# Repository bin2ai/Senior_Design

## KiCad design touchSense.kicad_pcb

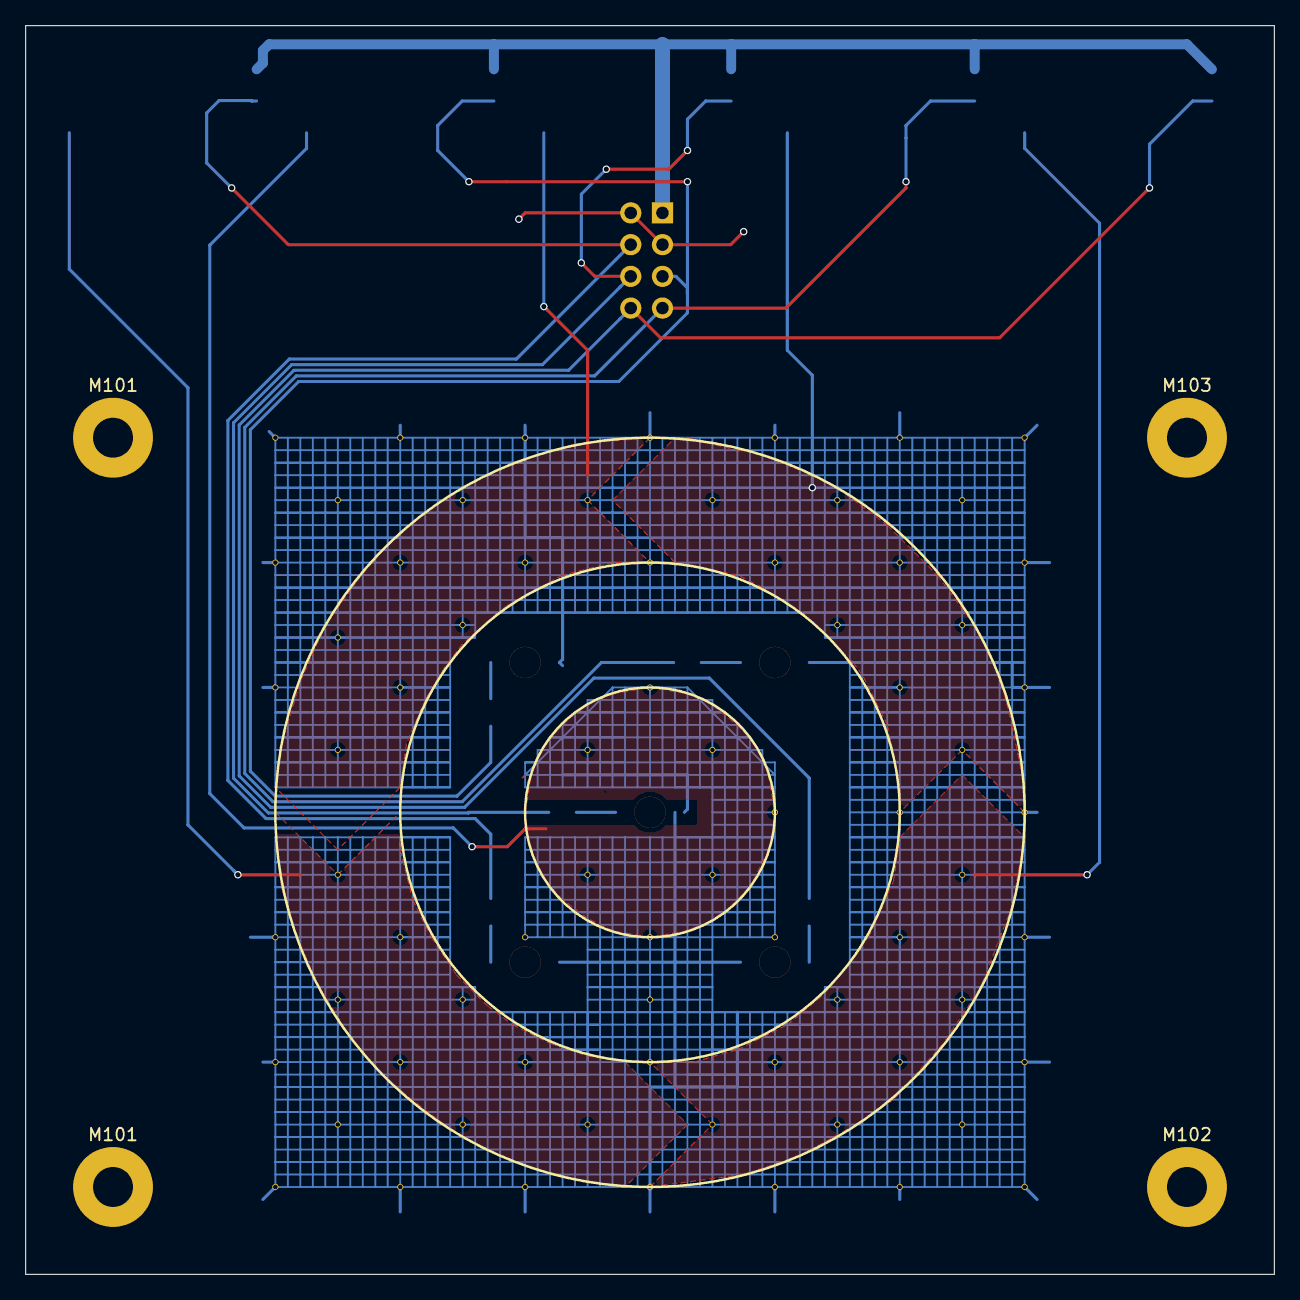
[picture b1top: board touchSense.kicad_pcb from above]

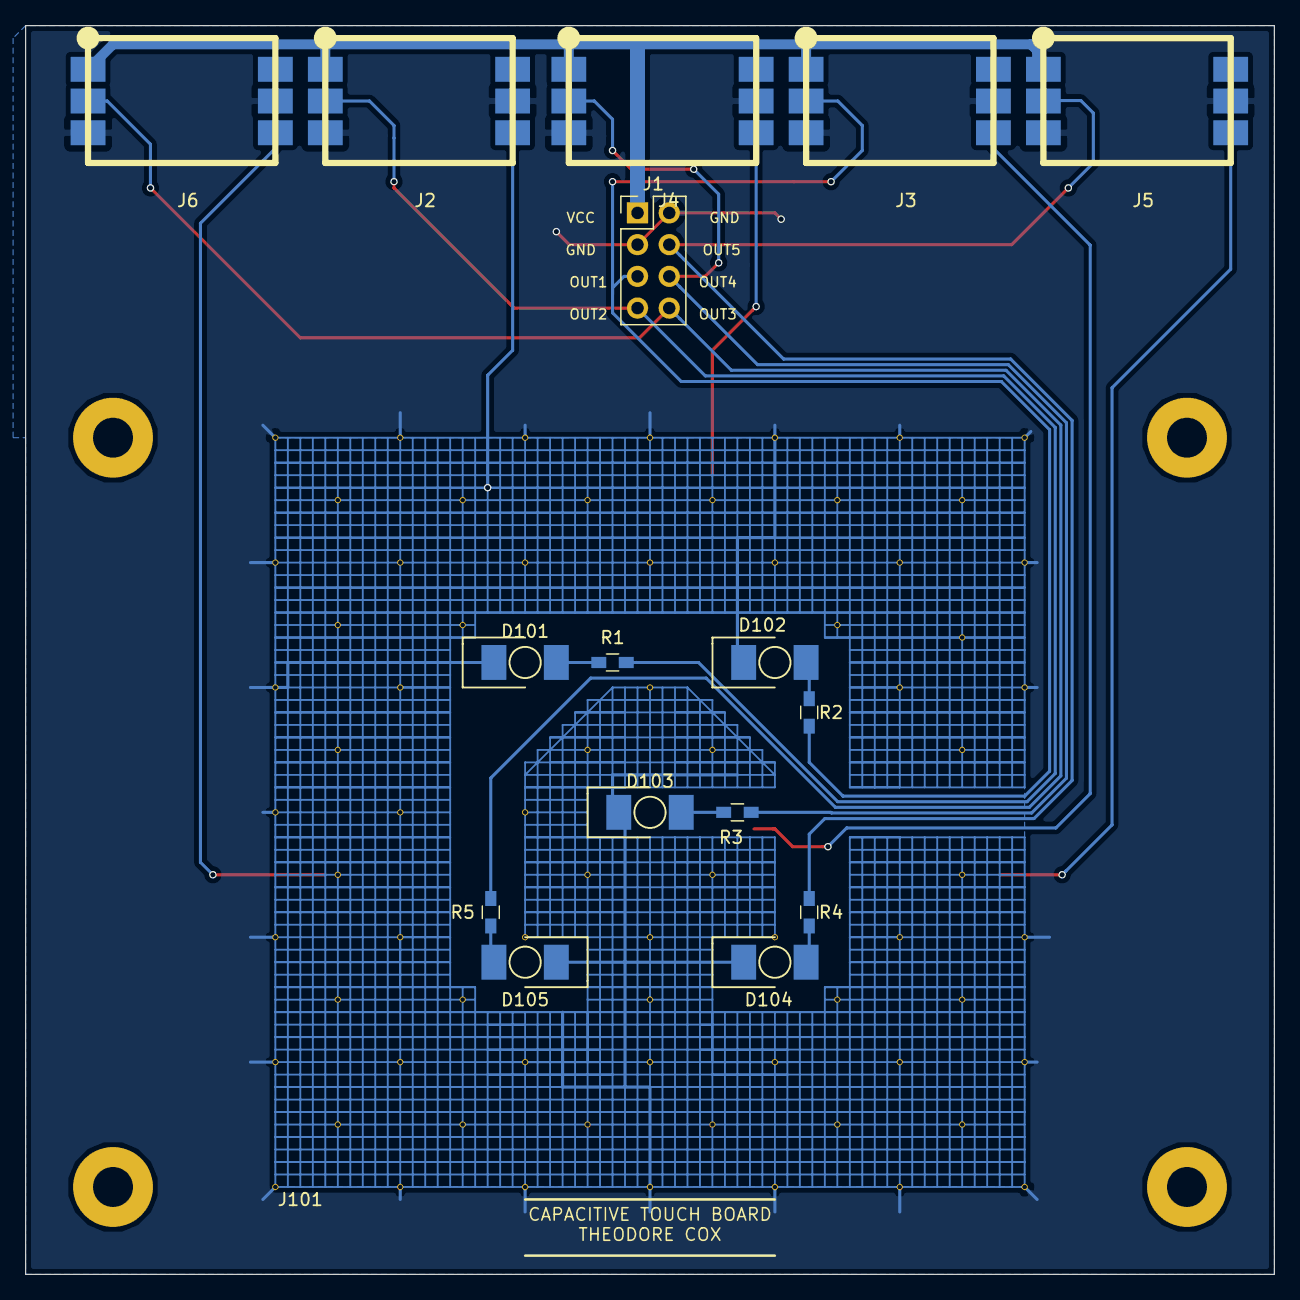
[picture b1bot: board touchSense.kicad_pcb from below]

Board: 2 copper layers, 100.0 x 100.0 mm, 21 parts (17 on the bottom side), 12 nets.

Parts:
D101, D102, D103, D104, D105: LED; LED_VLRK31Q1R2_REV_GUL
J1: breakout_MainBoard; Pin_Header_Straight_2x04_Pitch2.54mm
J2, J3, J4, J5, J6: CAPTOUC_castellated_Module; CAPTOUCH_castellated
J101: HATCHED_FILL; HATCHED_FILL_60mm_signalRouting
M101, M101#2, M102, M103: Mount; MountingHole_3.2mm_M3_Pad
R1, R2, R3, R4, R5: 500; R_0603_HandSoldering

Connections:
/OUT_1: J1.7, J2.2, R1.2
/OUT_2: J1.5, J3.2, R2.2
/OUT_3: J1.6, J4.2, R3.2
/OUT_4: J1.4, J5.2, R4.2
/OUT_5: J1.8, J6.2, R5.2
/VCC: J1.1, J2.1, J3.1, J4.1, J5.1, J6.1
GND: D101.1, D102.1, D103.1, D104.1, D105.1, J1.2, J1.3, J2.3, J2.5, J3.3, J3.5, J4.3, J4.5, J5.3, J5.5, J6.3, J6.5, J101.1
unnamed: D101.2, R1.1
unnamed: D102.2, R2.1
unnamed: D103.2, R3.1
unnamed: D104.2, R4.1
unnamed: D105.2, R5.1

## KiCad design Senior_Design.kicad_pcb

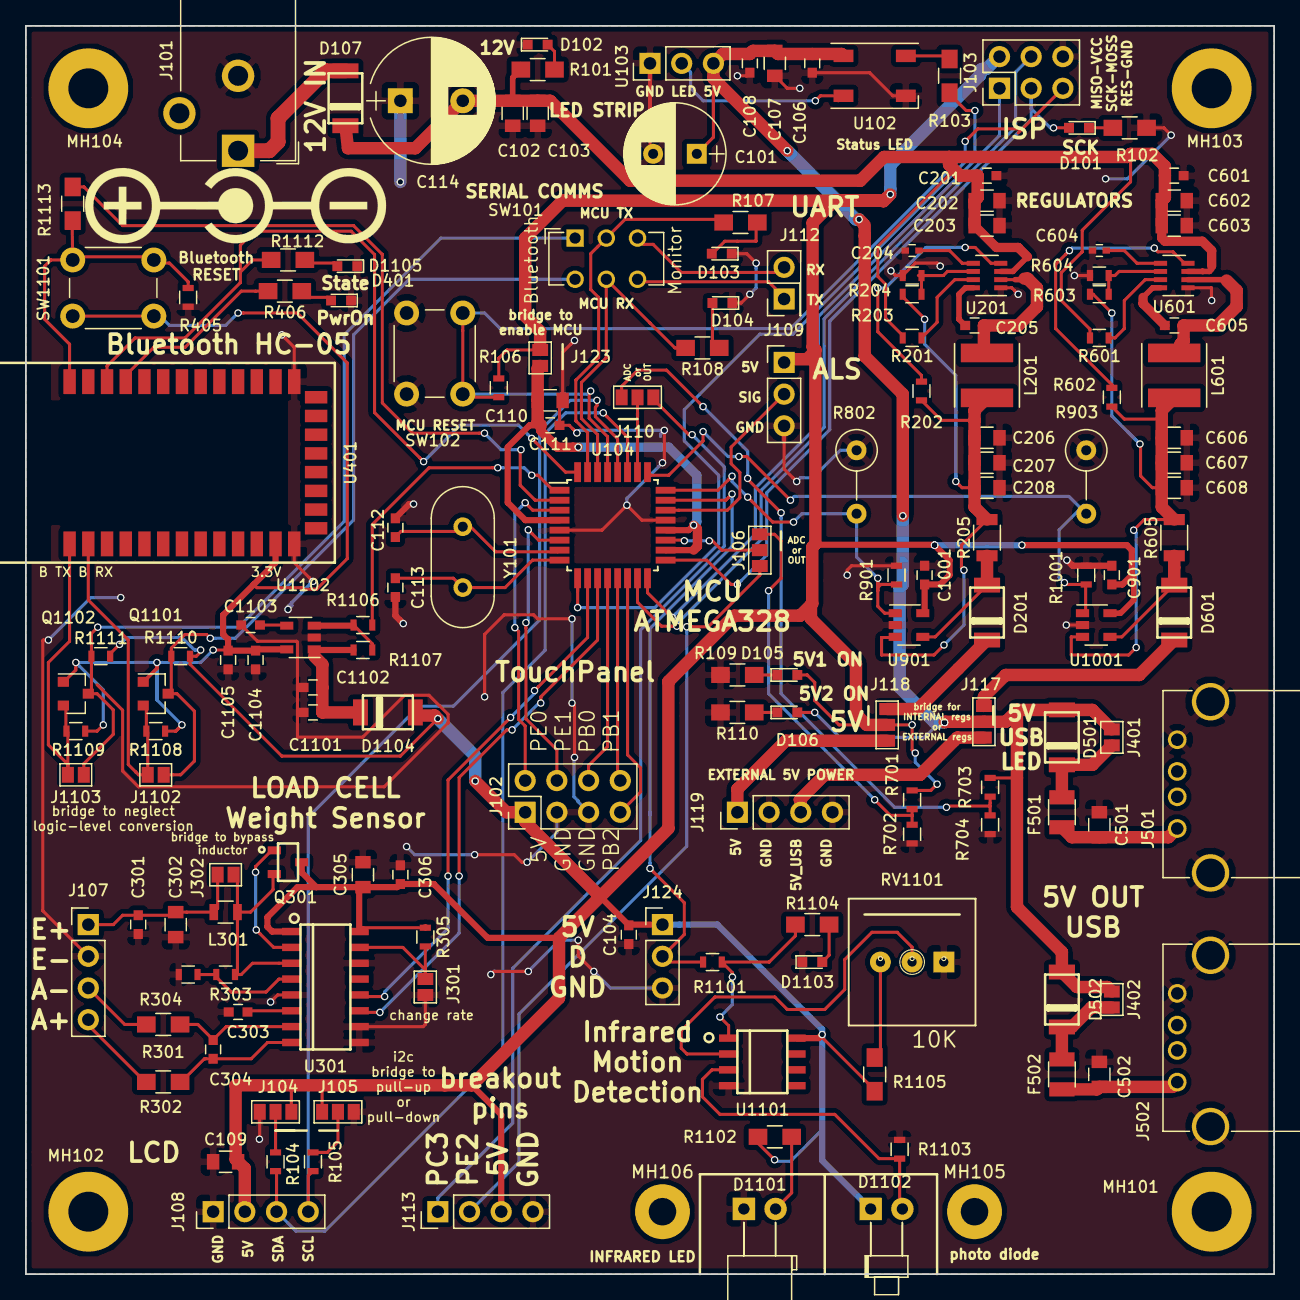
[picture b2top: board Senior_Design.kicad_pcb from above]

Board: 2 copper layers, 100.0 x 100.0 mm, 164 parts (0 on the bottom side), 101 nets.

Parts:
C101: ?uF; CP_Radial_D8.0mm_P3.50mm
C102, C103, C107, C109, C110, C202, C203, C302, C305, C501, C502, C602, C603: 10uF; C_0805
C104, C106, C108, C111, C201, C205, C301, C303, C304, C306, C601, C605, C901, C1001, C1101, C1103, C1104: 0.1uF; C_0603
C112, C113: 20pF; C_0603
C114: ?uF; CP_Radial_D10.0mm_P5.00mm
C204, C604: 8200pF; C_0402
C206, C207, C208, C606, C607, C608: 22uF; C_0805
C1102, C1105: 1uF; C_0603
D101, D102, D103, D104, D105, D106, D401, D1103, D1105: LED; LED_0603
D107, D201, D501, D502, D601, D1104: D_Schottky; SOD-128
D1101: IR204A; LED_D5.0mm_Horizontal_O3.81mm_Z3.0mm
D1102: D_Photo; LED_D1.8mm_W1.8mm_H2.4mm_Horizontal_O3.81mm_Z4.9mm
F501, F502: Polyfuse; Fuse_SMD1206_Reflow
J101: BARREL_JACK; Barrel_Jack_CUI_PJ-102AH
J102: touch(8pos) AT42QT1070 STANDALONE; Pin_Header_Straight_2x04_Pitch2.54mm
J103: ISP; Pin_Header_Straight_2x03_Pitch2.54mm
J104, J105, J106, J110, J117, J118: GS3
J107: LoadCell_Conn; Pin_Header_Straight_1x04_Pitch2.54mm
J108: Smraza2004_LCD; Pin_Header_Straight_1x04_Pitch2.54mm
J109: ambientLight; Pin_Header_Straight_1x03_Pitch2.54mm
J112: Serial Monitor; Pin_Header_Straight_2x01_Pitch2.54mm
J113: breakout; Pin_Header_Straight_1x04_Pitch2.54mm
J119: ext_5VPWR; Pin_Header_Straight_1x04_Pitch2.54mm
J123, J301, J302, J401, J402, J1102, J1103: GS2
J124: ext_Motion; Pin_Header_Straight_1x03_Pitch2.54mm
J501, J502: USB_A
L201, L601: 4.7uH; L_Taiyo-Yuden_MD-5050
L301: 3.3uH; L_0805
MH101, MH102, MH103, MH104: Mounting Hole; MountingHole_3.2mm_M3_Pad
MH105, MH106: IR LIGHT BLOCKER MOUNT; MountingHole_2.2mm_M2_Pad
Q301: MMBT4403; SOT23
Q1101, Q1102: BSS138; SOT-23
R101, R102, R103, R107, R108, R109, R110, R406, R1102, R1104, R1112, R1113: 500; R_0805_HandSoldering
R104, R105, R1107: 100K; R_0603
R106, R201, R601, R701, R702, R703, R704, R1101: 10k; R_0603
R202, R602: 100k; R_0603
R203, R603: 59k; R_0603
R204, R604: 10k_FB; R_0603
R205, R605: 0.1_SHUNT; R_1206
R301, R302, R1105: 100; R_0805_HandSoldering
R303: 20K; R_0603
R304: 8.2K; R_0603
R305, R405, R901, R1001, R1106, R1108, R1109, R1110, R1111: 10K; R_0603
R802, R903: RL; R_Axial_DIN0309_L9.0mm_D3.2mm_P5.08mm_Vertical
R1103: 54.9K; R_0603
RV1101: 10K; TSR-3386U
SW101: Serial Switch; SW_CuK_JS202011CQN_DPDT_Straight
SW102: RESET; SW_PUSH_6mm
SW1101: BLE_RESET; SW_PUSH_6mm
U102: WS2812B; LED_WS2812B-PLCC4
U103: WS2812B_STRIP; Pin_Header_Straight_1x03_Pitch2.54mm
U104: ATMEGA328PB-AU; TQFP-32_7x7mm_Pitch0.8mm
U201, U601: TPS563210ADDFT; SOT-23-8
U301: HX711; SOIC16
U401: MOUDLE-BLUETOOTH-HC-05(34P-27X13MM); HC-05
U901, U1001: INA169; SOT-23-5
U1101: LM358_IC; SOIC8
U1102: LP2985-3.3; SOT-23-5
Y101: 16MHZ; Crystal_HC49-U_Vertical

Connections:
5V1_monADC: J106.1, R701.2, R702.1
5V2_monADC: J110.1, R703.2, R704.1
5V-BUS: C104.2, C109.1, C305.2, C306.1, C901.1, C1001.1, D105.2, D1102.1, D1104.2, J102.1, J103.2, J104.3, J105.3, J108.2, J109.1, J113.3, J118.2, J123.2, J124.1, Q301.3, R106.1, R305.1, R701.1, R1102.1, R1105.1, R1110.2, R1111.2, U301.1, U301.16, U901.5, U1001.5, U1101.8
5V-BUS_USBLINE: C101.1, C106.2, C107.2, C108.2, D106.2, D501.2, D502.2, J117.2, J401.1, J402.1, R703.1, U102.1, U103.3
5V_curMon+: C206.1, C207.1, C208.1, L201.2, R202.1, R203.2, R205.2, U901.3
5V_curMon+_USBLINE: C606.1, C607.1, C608.1, L601.2, R602.1, R603.2, R605.2, U1001.3
5V_curMon-: D201.2, R205.1, U901.4
5V_curMon-_USBLINE: D601.2, R605.1, U1001.4
5V_curMon_ADC: R802.2, R901.2, U104.24, U901.1
5V_curMon_USBLINE_ADC: R903.2, R1001.2, U104.25, U1001.1
+12V: C102.1, C103.1, C114.2, C201.1, C202.1, C203.1, C601.1, C602.1, C603.1, D107.1, R101.2, R201.2, R601.2, U201.3, U601.3
/Bluetooth/3_3V: C1104.2, C1105.2, Q1101.1, Q1102.1, R1108.2, R1109.2, SW1101.2, U401.12, U1102.5
/Bluetooth/PwrOn: R406.2, U401.31
/Bluetooth/RX_3v3: J1102.2, Q1101.2, R1108.1, U401.2
/Bluetooth/TX_3v3: J1103.2, Q1102.2, R1109.1, U401.1
/RX: J112.2, SW101.3
/TX: J112.1, SW101.6
/_5V_SYS: D201.1, J118.1
/_5V_USB: D601.1, J117.1
BT_EN: R1106.2, U104.1
BT_KEY: R1113.2, U104.2
BT_STATE: R1112.2, U104.32, U401.32
B_RX: J1103.1, Q1102.3, R1111.1, SW101.1
B_TX: J1102.1, Q1101.3, R1110.1, SW101.4
GND: C101.2, C102.2, C103.2, C104.1, C106.1, C107.1, C108.1, C109.2, C110.1, C111.1, C112.2, C113.2, C114.1, C201.2, C202.2, C203.2, C204.2, C206.2, C207.2, C208.2, C301.2, C302.2, C303.2, C305.1, C306.2, C501.2, C502.2, C601.2, C602.2, C603.2, C604.2, C606.2, C607.2, C608.2, C901.2, C1001.2, C1101.1, C1102.1, C1103.1, C1104.1, C1105.1, D102.1, D103.1, D104.1, D401.1, D1101.1, D1103.1, D1105.1, J101.2, J102.3, J102.5, J103.6, J104.1, J105.1, J107.2, J108.1, J109.3, J113.4, J119.2, J119.4, J124.3, J301.2, J501.4, J501.5, J502.4, J502.5, R102.2, R109.2, R110.2, R204.1, R304.2, R405.1, R604.1, R702.2, R704.2, R802.1, R901.1, R903.1, R1001.1, R1103.2, RV1101.1, SW102.2, U102.3, U103.1, U104.5, U104.21, U201.1, U301.5, U301.9, U301.10, U301.14, U401.13, U401.22, U601.1, U901.2, U1001.2, U1101.4, U1102.2
LEDS_Din: U102.2, U103.2
LED_Din: R103.1, U104.9
MCU_RX: R108.2, SW101.5, U104.30
MCU_TX: R107.2, SW101.2, U104.31
MISO: J103.1, U104.16
MOSI: J103.4, U104.15
Motion_Signal: J124.2, R1101.2, U104.23
unnamed: C110.2, C111.2, J123.1, U104.4, U104.18, U104.20
unnamed: C112.1, U104.7, Y101.2
unnamed: C113.1, U104.8, Y101.1
unnamed: C204.1, U201.5
unnamed: C205.1, U201.8
unnamed: C205.2, L201.1, U201.2
unnamed: C303.1, U301.6
unnamed: C304.1, R301.1, U301.7
unnamed: C304.2, R302.1, U301.8
unnamed: C501.1, F501.2, J501.1
unnamed: C502.1, F502.2, J502.1
unnamed: C604.1, U601.5
unnamed: C605.1, U601.8
unnamed: C605.2, L601.1, U601.2
unnamed: C1101.2, C1102.2, D1104.1, R1107.1, U1102.1
unnamed: C1103.2, U1102.4
unnamed: D101.1, R102.1
unnamed: D102.2, R101.1
unnamed: D103.2, R107.1
unnamed: D104.2, R108.1
unnamed: D105.1, R109.1
unnamed: D106.1, R110.1
unnamed: D107.2, J101.1
unnamed: D401.2, R406.1
unnamed: D501.1, F501.1, J401.2
unnamed: D502.1, F502.1, J402.2
unnamed: D1101.2, R1102.2
unnamed: D1102.2, R1103.1, U1101.3
unnamed: D1103.2, R1104.2
unnamed: D1105.2, R1112.1
unnamed: J104.2, R104.2
unnamed: J105.2, R105.2
unnamed: J106.2, U104.19
unnamed: J110.2, U104.26
unnamed: J117.3, J119.3
unnamed: J118.3, J119.1
unnamed: J301.1, R305.2, U301.15
unnamed: J302.1, L301.2, Q301.2, R303.1, U301.3
unnamed: Q301.1, U301.2
unnamed: R103.2, U102.4
unnamed: R201.1, U201.7
unnamed: R202.2, U201.4
unnamed: R203.1, R204.2, U201.6
unnamed: R303.2, R304.1, U301.4
unnamed: R601.1, U601.7
unnamed: R602.2, U601.4
unnamed: R603.1, R604.2, U601.6
unnamed: R1101.1, R1104.1, U1101.1
unnamed: R1105.2, RV1101.3
unnamed: R1106.1, R1107.2, U1102.3
unnamed: R405.2, R1113.1, SW1101.1, U401.34
unnamed: RV1101.2, U1101.2
RESET: J103.5, R106.2, SW102.1, U104.29
SCALE_A+: J107.4, R302.2
SCALE_A-: J107.3, R301.2
SCALE_DOUT: U104.10, U301.12
SCALE_E+: C301.1, C302.1, J107.1, J302.2, L301.1
SCALE_PD_SCK: U104.11, U301.11
SCK: D101.2, J103.3, U104.17
SCL: J108.4, R105.1, U104.28
SDA: J108.3, R104.1, U104.27
ambientLight: J109.2, U104.22
breakout_1A: J110.3, J113.1
breakout_2A: J106.3, J113.2
touch_1: J102.6, U104.12
touch_2: J102.8, U104.13
touch_3: J102.7, U104.14
touch_4: J102.2, U104.3
touch_5: J102.4, U104.6

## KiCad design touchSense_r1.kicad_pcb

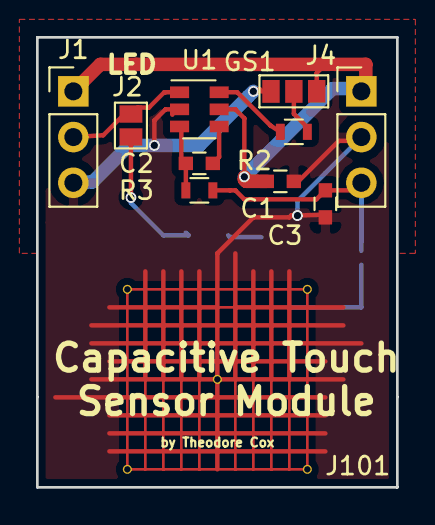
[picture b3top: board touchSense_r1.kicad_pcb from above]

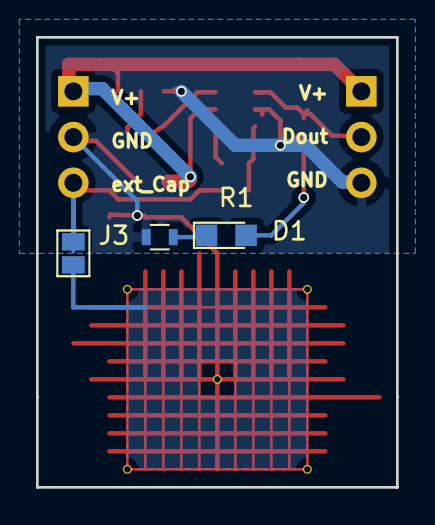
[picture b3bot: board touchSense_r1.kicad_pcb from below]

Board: 2 copper layers, 20.0 x 25.0 mm, 14 parts (3 on the bottom side), 10 nets.

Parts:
C1: 0.1uF; C_0603
C2: 4.7nF; C_0603
C3: 5pF; C_0603
D1: LED; LED_0805
GS1: GS3
J1: breakout; Pin_Header_Straight_1x03_Pitch2.54mm
J2, J3: GS2
J4: cap/daisy; Pin_Header_Straight_1x03_Pitch2.54mm
J101: Hatched_Fill; HATCHED_FILL_10mm
R1, R2: 1K; R_0603
R3: 10K; R_0603
U1: AT42QT1010-TSHR; SOT-23-6

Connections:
/CAP_PAD: C3.1, J3.1, J4.3, R3.1
/OUT1: J1.2, J2.2, U1.1
/VDD: C1.1, GS1.1, J1.1, J4.1, U1.5
GND: C1.2, C3.2, GS1.3, J1.3, J4.2, J101.1, R1.1, U1.2
unnamed: C2.1, R3.2, U1.3
unnamed: C2.2, U1.4
unnamed: D1.1, R1.2
unnamed: D1.2, J2.1
unnamed: GS1.2, R2.1
unnamed: R2.2, U1.6

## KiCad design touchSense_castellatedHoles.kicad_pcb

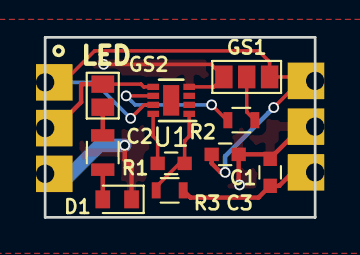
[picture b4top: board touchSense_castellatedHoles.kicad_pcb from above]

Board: 2 copper layers, 15.0 x 10.0 mm, 12 parts (0 on the bottom side), 9 nets.

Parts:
C1: 0.1uF; C_0603
C2: 4.7nF; C_0603
C3: 5pF; C_0603
D1: LED_0603_1608Metric
GS1: GS3
GS2: GS2
J1: breakout; CONN_01x03_CastellatedHole_Pad_1mmDrill
J?: CONN_01X03_CASTELLATED; CONN_01x03_CastellatedHole_Pad_1mmDrill
R1: R_0805
R2: 1K; R_0603
R3: 10K; R_0603
U1: VDFN-8-1EP_2x2mm_Pitch0.5mm

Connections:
/CAP_PAD: C3.1, J?.6, R3.1
/OUT1: GS2.2, J1.2, U1.5
/VDD: C1.1, GS1.1, J1.1, J?.4, U1.7
GND: C1.2, C3.2, D1.1, GS1.3, J1.3, J?.5, U1.4
unnamed: C2.1, R3.2, U1.1
unnamed: C2.2, U1.8
unnamed: GS2.1, R1.1
unnamed: GS1.2, R2.1
unnamed: R2.2, U1.6

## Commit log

2018-04-23 aded motion sense sheet
2018-04-23 new touch sense schematic
    different part AT42QT1010/1011
2018-04-23 changed to ATMEGA2560
2018-04-23 added usb-serial schematic
2018-04-24 added 12V power schematic
2018-04-24 created current monitor schematic
2018-04-24 current Monitor schematic edit
2018-04-24 last edit of the night 4-24
2018-04-24 added bom current as of 4-24
2018-04-24 bom format fix
2018-04-24 added FTDI chip to bom
2018-05-13 started PCB layout
2018-05-14 hc-05 and buzzer 3d model
2018-06-01 after group meeting
2018-06-05 MCU Change ATMEGA328PB
2018-06-05 all components on board, needs routing
2018-06-06 before meeting
2018-06-07 traces started
2018-06-08 99 percent ready to order
2018-06-09 finalized pcblayouts, before uploading to manufacturer
2018-06-10 new touch implementation
2018-06-10 organize project folder, small pcb maitenance, generated gerbers
2018-06-17 after mock cdr
